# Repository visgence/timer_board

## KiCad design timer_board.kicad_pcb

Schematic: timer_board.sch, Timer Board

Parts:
BT1: BATTERY
C1, C8: CP1
C2, C3, C4, C5, C6, C7, C10: 1uF
C9: C
CON1: AVR-ISP-6
D1: Relay
D2: DIODE
D3: Power
D4: Trigger
DS1: 2X16_LCD
F1: FUSE
IC1: ATMEGA32U4; TQFP44
K1: T9AS5D22-5
P1: USBMICRO
P2: OUT_INV
P3: Trigger
P4: OUT
P5: ADC
P6: CONN_1
Q1, Q2: NPN
R1, R2, R8, R9, R13, R19: 10k
R3, R18: 1k
R4, R12, R16, R17: 2.2k
R5, R6, R7, R10, R11: 5k
R14, R15: 22
RV1: POT
S1: UP
S2: DOWN
S3: LEFT
S4: RIGHT
S5: SELECT
S6: RESET
U1: DS3231MZ
U2: 74HC04
Y1: RESONATORSMD

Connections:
+5V: C1.1, C8.1, C9.1, CON1.2, D2.2 (K), DS1.2 (VDD), DS1.15 (LED+), F1.2, IC1.14 (VCC), IC1.24 (AVCC), IC1.34 (VCC), IC1.42 (AREF), IC1.44 (AVCC), K1.2, R1.1, R2.1, R4.2, R5.2, R6.2, R7.2, R8.1, R9.1, R10.2, R11.2, R13.1, R16.2, R18.2, R19.1, RV1.1, U1.2 (Vcc), U2.14 (VCC)
BACK: IC1.40 ((ADC1)PF1), R12.2
DB4: DS1.11 (DB4), IC1.25 ((ICP1/ADC8)PD4)
DB5: DS1.12 (DB5), IC1.22 ((XCK1/~CTS~)PD5)
DB6: DS1.13 (DB6), IC1.26 ((T1/~OC4D~/ADC9)PD6)
DB7: DS1.14 (DB7), IC1.27 ((T0/OC4D/ADC10)PD7)
Down: C3.1, IC1.30 ((PCINT6/OC1B/OC4B/ADC13)PB6), R6.1, S2.1, S2.2
E: DS1.6 (E), IC1.38 ((ADC5/TMS)PF5)
GND: BT1.2 (-), C1.2, C2.2, C3.2, C4.2, C5.2, C6.2, C7.2, C8.2, C9.2, C10.1, CON1.6, D3.2 (K), D4.2 (K), DS1.1 (VSS), IC1.5 (UGnd), IC1.15 (GND), IC1.23 (GND), IC1.35 (GND), IC1.43 (GND), P1.4 (SH), P1.5 (GND), P2.2 (PM), P3.2 (PM), P4.2 (PM), P5.2 (PM), Q1.1 (E), Q2.1 (E), RV1.3, S1.3, S1.4, S2.3, S2.4, S3.3, S3.4, S4.3, S4.4, S5.3, S5.4, S6.1, S6.2, U1.5 (GND), U2.7 (GND), Y1.2
Left: C4.1, IC1.29 ((PCINT5/OC1A/~OC4B~/ADC12)PB5), R7.1, S3.1, S3.2
unnamed: P2.1, U2.6, U2.9
unnamed: IC1.20 ((RXD1/INT2)PD2), U2.2
unnamed: P4.1, U2.8
unnamed: Q2.2 (B), R12.1
unnamed: DS1.16 (LED-), Q2.3 (C)
unnamed: D3.1 (A), R16.1
unnamed: P1.2 (D-), R14.1
unnamed: P1.3 (D+), R15.1
unnamed: IC1.3 (D-), R14.2
unnamed: IC1.4 (D+), R15.2
unnamed: R9.2, U1.4 (!(Reset))
unnamed: C7.1, IC1.6 (Ucap)
unnamed: D1.2 (K), D2.1 (A), K1.3, Q1.3 (C)
unnamed: Q1.2 (B), R3.2
unnamed: CON1.4, IC1.10 ((PDI/PCINT2/MOSI)PB2)
unnamed: CON1.1, IC1.11 ((PDO/PCINT3/MISO)PB3)
unnamed: R8.2, U1.3 (!(INT)/SQR)
unnamed: BT1.1 (+), U1.6 (Vbat)
unnamed: IC1.41 ((ADC0)PF0), P5.1
unnamed: P6.1, R19.2, U1.1 (32KHz)
unnamed: R17.1, U2.1, U2.4
unnamed: D4.1 (A), R17.2
unnamed: D1.1 (A), R4.1
unnamed: DS1.3 (V0), RV1.2
unnamed: IC1.16 (XTAL2), Y1.1
unnamed: CON1.3, IC1.9 ((PCINT1/SCLK)PB1)
unnamed: IC1.17 (XTAL1), Y1.3
unnamed: C10.2, P3.1, R18.1, U2.3
OUT: IC1.21 ((TXD1/INT3)PD3), U2.5
RELAY: IC1.39 ((ADC4/TCK)PF4), R3.1
RS: DS1.4 (RS), IC1.36 ((ADC7/TDI)PF7)
RW: DS1.5 (R/W), IC1.37 ((ADC6/TDO)PF6)
Right: C5.1, IC1.28 ((PCINT4/ADC11)PB4), R10.1, S4.1, S4.2
SCL: IC1.18 ((OC0B/SCL/INT0)PD0), R2.2, U1.8 (SCL)
SDA: IC1.19 ((SDA/INT1)PD1), R1.2, U1.7 (SDA)
Select: C6.1, IC1.32 ((ICP3/CLK0/OC4A)PC7), R11.1, S5.1, S5.2
UP: C2.1, IC1.12 ((PCINT7/OC0A/OC1C/~RTS~)PB7), R5.1, S1.1, S1.2
UVCC: F1.1, IC1.2 (UVcc), IC1.7 (VBus), P1.1 (Vcc)
reset: CON1.5, IC1.13 (~RESET~), R13.2, S6.3, S6.4

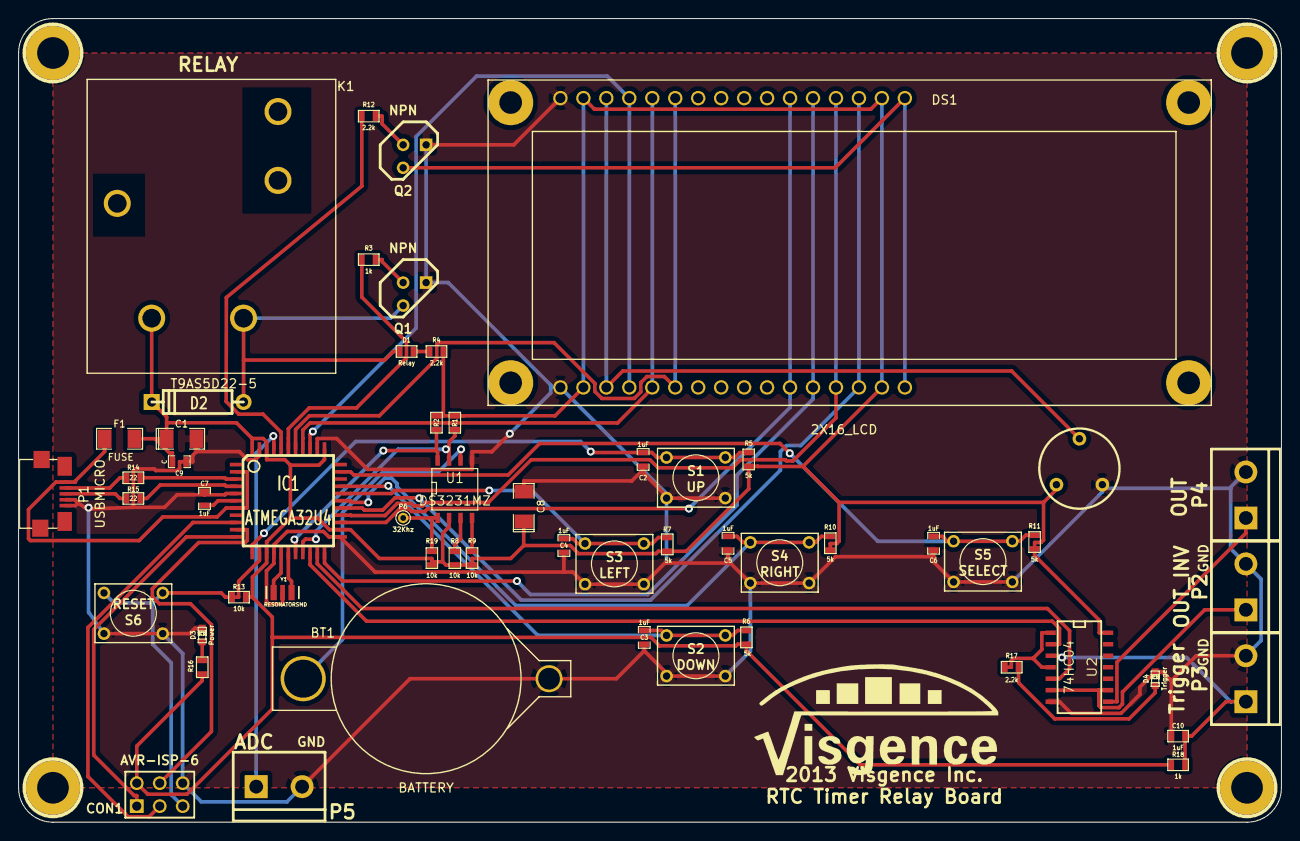
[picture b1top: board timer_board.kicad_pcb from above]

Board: 2 copper layers, 139.7 x 88.9 mm, 62 parts (0 on the bottom side), 49 nets.

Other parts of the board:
G1: LOGO
p10, p11, p12, p13: pin; 1pin_C

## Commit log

2013-06-22 Started timer board project
2013-06-23 Put in more work on schematic
2013-06-28 Added LCD and battery holder to schematic
2013-06-28 forgot to save
2013-06-30 Added Relay
2013-07-03 Added buttons
2013-07-03 Added title to sheet
2013-07-03 Added Reset
2013-07-04 Grounded switches, added trigger and output
2013-07-04 Fixed up a few bad connections
2013-07-04 Started workin on layout
2013-07-07 Added LCD and USB Micro
2013-07-07 moved a few things arround
2013-07-07 Added battery holder
2013-07-08 Added proper package for RTC and inverter
2013-07-08 Added Pot
2013-07-08 Modified Push button
2013-07-08 Added AVR ISP header
2013-07-08 Moved stuff arround so every thing fits in outline
2013-07-08 Made holes a little bitter on lcd module
2013-07-11 Moved resistors arround
2013-07-11 Updated kicad to 4022 and moved resistors
2013-07-11 Modified LCD
2013-07-11 Added test point for 32khz, moved parts arround
2013-07-11 Added mounting holes
2013-07-11 Routed board
2013-07-24 added firmware
2013-07-26 added I2C address of clock
2013-07-26 adds proof-of-concept RTC code
2013-07-26 removed adjustment of clock and increases delay for better testing
2013-07-26 Got the LCD to work, totally a mess, need to clean
2013-07-27 Cleaned up code a lot, Using modified LCD lib
2013-07-27 Added Modified LiquidCrystal Library
2013-07-27 Clock now display time on LCD
2013-07-27 Got buttons and trigger working
